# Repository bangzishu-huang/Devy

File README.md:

# Devy
My own first-ever custom devboard! It will also include a LED which turns on and off.

This project was one of the first times I designed a complex PCB and I'm going to be honest it was really hard to learn how to create this at first. I think I spent around 3-4 days trying to understand how to do everything, from the schematics to the actual PCB design. In the end, though, I'm really happy that I was able to learn how to create it and this will probably be one of those projects I'll remember for a very long time.

# Final Pictures
Here are the pictures of my devboard after it was successfully soldered!
- Front
- 

- Back
- 

# PCB
I used KiCad for every step of creating Devy, and it saved me a lot of time I would say.

- Schematic
- 

- PCB with zones (GND as net)
- 

# 3D Model
Below are views of Devy taken through KiCad's 3D model viewer. I have to say my silkscreen is the best.

- Front
- 

- Back
- 

# Firmware
Here, I used KMK to just make the LED turn on and off. It acts as a check up on the devboard to make sure everything would work.

# BOM (Bill of Materials)
|Quantity|Footprint|
|---|---|
|15|C_0402_1005Metric|
|8|R_0402_1005Metric|
|2|C_0603_1608Metric|
|2|PinHeader_1x20_P2.54mm_Vertical|
|1|PinHeader_1x03_P2.54mm_Vertical|
|1|Crystal_SMD_3225-4Pin_3.2x2.5mm|
|1|SW_Push_SPST_NO_Alps_SKRK|
|1|USB_C_Receptacle_HRO_TYPE-C-31-M-12|
|1|QFN-56-1EP_7x7mm_P0.4mm_EP3.2x3.2mm|
|1|LED_WS2812B-2020_PLCC4_2.0x2.0mm|
|1|Winbond_USON-8-1EP_3x2mm_P0.5mm_EP0.2x1.6mm|
|1|SOT-23|

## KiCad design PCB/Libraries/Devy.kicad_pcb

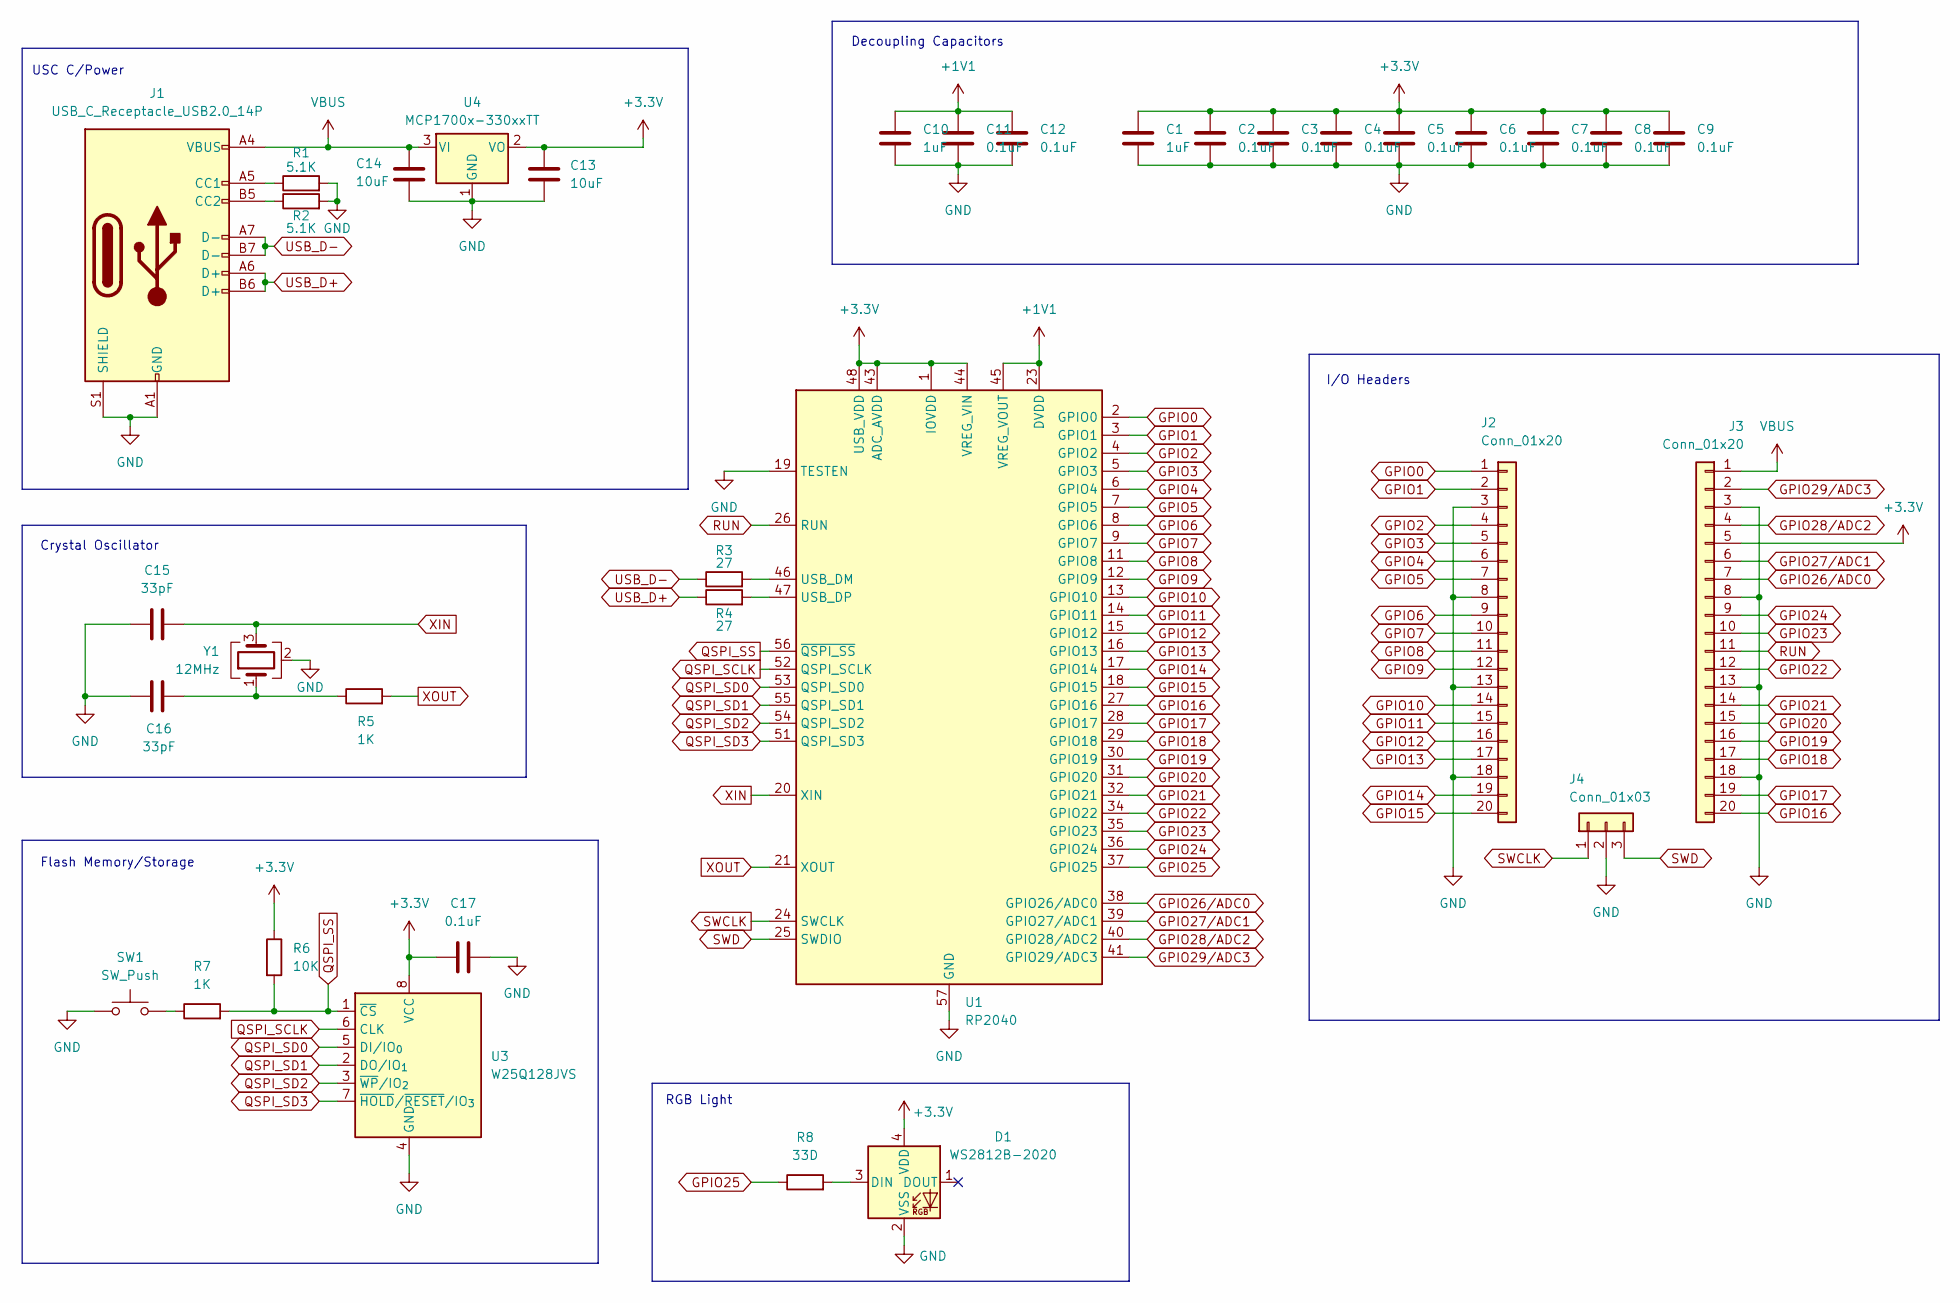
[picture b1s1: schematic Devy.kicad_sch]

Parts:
C1, C10: 1uF; C_0402_1005Metric
C2, C3, C4, C5, C6, C7, C8, C9, C11, C12, C17: 0.1uF; C_0402_1005Metric
C13, C14: 10uF; C_0603_1608Metric
C15, C16: 33pF; C_0402_1005Metric
D1: WS2812B-2020; LED_WS2812B-2020_PLCC4_2.0x2.0mm
J1: USB_C_Receptacle_USB2.0_14P; USB_C_Receptacle_HRO_TYPE-C-31-M-12
J2, J3: Conn_01x20; PinHeader_1x20_P2.54mm_Vertical
J4: Conn_01x03; PinHeader_1x03_P2.54mm_Vertical
R1, R2: 5.1K; R_0402_1005Metric
R3, R4: 27; R_0402_1005Metric
R5, R7: 1K; R_0402_1005Metric
R6: 10K; R_0402_1005Metric
R8: 33D; R_0402_1005Metric
SW1: SW_Push; SW_Push_SPST_NO_Alps_SKRK
U1: RP2040; QFN-56-1EP_7x7mm_P0.4mm_EP3.2x3.2mm
U3: W25Q128JVS; Winbond_USON-8-1EP_3x2mm_P0.5mm_EP0.2x1.6mm
U4: MCP1700x-330xxTT; SOT-23
Y1: 12MHz; Crystal_SMD_3225-4Pin_3.2x2.5mm

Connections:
+1V1: C10.1, C11.1, C12.1, U1.23 (DVDD), U1.45 (VREG_VOUT), U1.50 (DVDD)
+3.3V: C1.1, C2.1, C3.1, C4.1, C5.1, C6.1, C7.1, C8.1, C9.1, C13.1, C17.1, D1.4 (VDD), J3.5, R6.1, U1.1 (IOVDD), U1.10 (IOVDD), U1.22 (IOVDD), U1.33 (IOVDD), U1.42 (IOVDD), U1.43 (ADC_AVDD), U1.44 (VREG_VIN), U1.48 (USB_VDD), U1.49 (IOVDD), U3.8 (VCC), U4.2 (VO)
GND: C1.2, C2.2, C3.2, C4.2, C5.2, C6.2, C7.2, C8.2, C9.2, C10.2, C11.2, C12.2, C13.2, C14.2, C15.1, C16.1, C17.2, D1.2 (VSS), J1.A1 (GND), J1.A12 (GND), J1.B1 (GND), J1.B12 (GND), J1.S1 (SHIELD), J2.3, J2.8, J2.13, J2.18, J3.3, J3.8, J3.13, J3.18, J4.2, R1.2, R2.2, SW1.1, U1.19 (TESTEN), U1.57 (GND), U3.4 (GND), U4.1 (GND), Y1.2 (G), Y1.4 (G)
GPIO0: J2.1, U1.2 (GPIO0)
GPIO1: J2.2, U1.3 (GPIO1)
GPIO2: J2.4, U1.4 (GPIO2)
GPIO3: J2.5, U1.5 (GPIO3)
GPIO4: J2.6, U1.6 (GPIO4)
GPIO5: J2.7, U1.7 (GPIO5)
GPIO6: J2.9, U1.8 (GPIO6)
GPIO7: J2.10, U1.9 (GPIO7)
GPIO8: J2.11, U1.11 (GPIO8)
GPIO9: J2.12, U1.12 (GPIO9)
GPIO10: J2.14, U1.13 (GPIO10)
GPIO11: J2.15, U1.14 (GPIO11)
GPIO12: J2.16, U1.15 (GPIO12)
GPIO13: J2.17, U1.16 (GPIO13)
GPIO14: J2.19, U1.17 (GPIO14)
GPIO15: J2.20, U1.18 (GPIO15)
GPIO16: J3.20, U1.27 (GPIO16)
GPIO17: J3.19, U1.28 (GPIO17)
GPIO18: J3.17, U1.29 (GPIO18)
GPIO19: J3.16, U1.30 (GPIO19)
GPIO20: J3.15, U1.31 (GPIO20)
GPIO21: J3.14, U1.32 (GPIO21)
GPIO22: J3.12, U1.34 (GPIO22)
GPIO23: J3.10, U1.35 (GPIO23)
GPIO24: J3.9, U1.36 (GPIO24)
GPIO25: R8.1, U1.37 (GPIO25)
GPIO26/ADC0: J3.7, U1.38 (GPIO26/ADC0)
GPIO27/ADC1: J3.6, U1.39 (GPIO27/ADC1)
GPIO28/ADC2: J3.4, U1.40 (GPIO28/ADC2)
GPIO29/ADC3: J3.2, U1.41 (GPIO29/ADC3)
unnamed: C16.2, R5.1, Y1.1
unnamed: D1.3 (DIN), R8.2
unnamed: J1.A5 (CC1), R1.1
unnamed: J1.B5 (CC2), R2.1
unnamed: R7.1, SW1.2
unnamed: R3.2, U1.46 (USB_DM)
unnamed: R4.2, U1.47 (USB_DP)
QSPI_SCLK: U1.52 (QSPI_SCLK), U3.6 (CLK)
QSPI_SD0: U1.53 (QSPI_SD0), U3.5 (DI/IO_{0})
QSPI_SD1: U1.55 (QSPI_SD1), U3.2 (DO/IO_{1})
QSPI_SD2: U1.54 (QSPI_SD2), U3.3 (~WP/IO_{2})
QSPI_SD3: U1.51 (QSPI_SD3), U3.7 (~HOLD/~RESET/IO_{3})
QSPI_SS: R6.2, R7.2, U1.56 (~QSPI_SS), U3.1 (~CS)
RUN: J3.11, U1.26 (RUN)
SWCLK: J4.1, U1.24 (SWCLK)
SWD: J4.3, U1.25 (SWDIO)
USB_D+: J1.A6 (D+), J1.B6 (D+), R4.1
USB_D-: J1.A7 (D-), J1.B7 (D-), R3.1
VBUS: C14.1, J1.A4 (VBUS), J1.A9 (VBUS), J1.B4 (VBUS), J1.B9 (VBUS), J3.1, U4.3 (VI)
XIN: C15.2, U1.20 (XIN), Y1.3
XOUT: R5.2, U1.21 (XOUT)

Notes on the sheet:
Decoupling Capacitors
Flash Memory/Storage
RGB Light
USC C/Power
Crystal Oscillator
I/O Headers

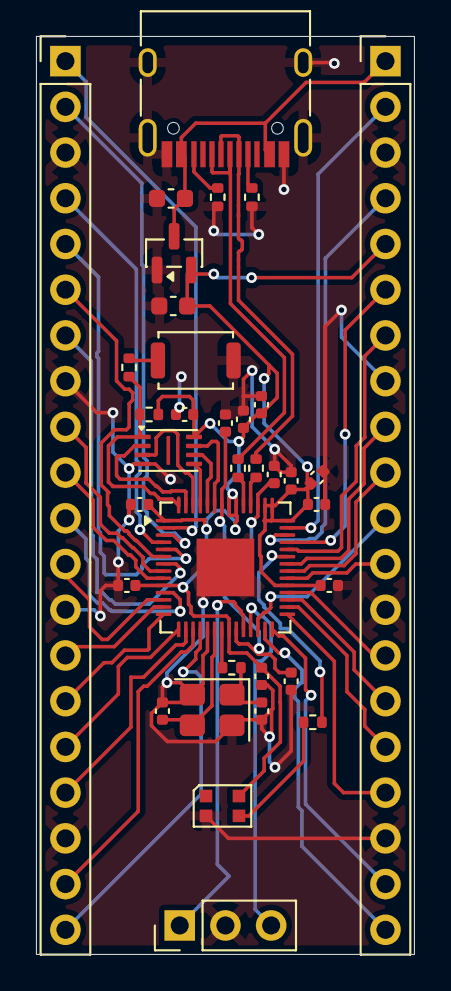
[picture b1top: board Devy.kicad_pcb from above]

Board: 2 copper layers, 21.0 x 51.0 mm, 36 parts (1 on the bottom side), 54 nets.

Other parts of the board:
Devy by Bangzishu Huang: LOGO

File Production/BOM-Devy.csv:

Comment,Designator,Footprint,LCSC,Quantity
0.1uF,C7,C_0402_1005Metric,,1
5.1K,R1,R_0402_1005Metric,,1
0.1uF,C12,C_0402_1005Metric,,1
0.1uF,C11,C_0402_1005Metric,,1
0.1uF,C5,C_0402_1005Metric,,1
10uF,C13,C_0603_1608Metric,,1
0.1uF,C9,C_0402_1005Metric,,1
33pF,C15,C_0402_1005Metric,,1
1K,R7,R_0402_1005Metric,,1
WS2812B-2020,D1,LED_WS2812B-2020_PLCC4_2.0x2.0mm,,1
0.1uF,C4,C_0402_1005Metric,,1
0.1uF,C8,C_0402_1005Metric,,1
10uF,C14,C_0603_1608Metric,,1
10K,R6,R_0402_1005Metric,,1
W25Q128JVS,U3,Winbond_USON-8-1EP_3x2mm_P0.5mm_EP0.2x1.6mm,,1
1K,R5,R_0402_1005Metric,,1
0.1uF,C6,C_0402_1005Metric,,1
Conn_01x20,J2,PinHeader_1x20_P2.54mm_Vertical,,1
0.1uF,C2,C_0402_1005Metric,,1
Conn_01x03,J4,PinHeader_1x03_P2.54mm_Vertical,,1
MCP1700x-330xxTT,U4,SOT-23,,1
1uF,C1,C_0402_1005Metric,,1
0.1uF,C3,C_0402_1005Metric,,1
12MHz,Y1,Crystal_SMD_3225-4Pin_3.2x2.5mm,,1
27,R4,R_0402_1005Metric,,1
1uF,C10,C_0402_1005Metric,,1
0.1uF,C17,C_0402_1005Metric,,1
SW_Push,SW1,SW_Push_SPST_NO_Alps_SKRK,,1
USB_C_Receptacle_USB2.0_14P,J1,USB_C_Receptacle_HRO_TYPE-C-31-M-12,,1
5.1K,R2,R_0402_1005Metric,,1
RP2040,U1,QFN-56-1EP_7x7mm_P0.4mm_EP3.2x3.2mm,,1
33D,R8,R_0402_1005Metric,,1
27,R3,R_0402_1005Metric,,1
Conn_01x20,J3,PinHeader_1x20_P2.54mm_Vertical,,1
33pF,C16,C_0402_1005Metric,,1

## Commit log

2026-03-11 Added .DS_Store to .gitignore
2026-03-11 Added to pcb libraries and assets
2026-03-11 added schematic pic and production files
2026-03-11 added firmware
2026-03-11 Enhance README with project details and images
    Expanded the README to include details about the project, PCB design process, and components used.
2026-04-19 added final pictures
2026-04-19 Add final pictures of the devboard to README
    Added final pictures of the devboard after soldering.
